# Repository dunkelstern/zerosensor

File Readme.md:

# Raspberry Pi Zero Sensor breakout board

<br />This work is licensed under a <a rel="license" href="http://creativecommons.org/licenses/by-sa/4.0/">Creative Commons Attribution-ShareAlike 4.0 International License</a>.

- 2 Level-Shifted SPI Ports
- 1 Level-Shifted I2C Port (Stemma/Grove/Quiic compatible)
- 1 Level-Shifted UART Port
- 4 Analog Inputs with onboard I2C ADC (MAX116xx-Series)
- 1 I2S Port (3.3V only)
- 2 Buttons on GPIO Pins
- 1 LED on GPIO Pin
- Power MOSFET on PWM Pin (Max 20V 8.5A)
- (optional) External Power In via Power MOSFET Screw-Terminal with 5V Regulator
- (optional) Extra 3.3V LDO to avoid introducing fault current into Raspi 3.3V rail
- (optional) Hat EEPROM for auto-configuration

## Before use

**Please read this document before use, you have to set some solder jumpers to use the board!**

- [BOM](bom.html)
- Gerbers are in `gerber` sub-directory
- SVG renders for manual UV exposing copper plated boards for etching yourself are in `svg` (be aware: this PCB has 86 vias and all through holes are supposed to be plated through!)
- Assembly files with values of resistors, etc are in `assembly`
- You can find a STEP file in `assembly` too

## SPI

There are 2 SPI ports broken out, they share MISO, MOSI and SCK lines and the chip enable
pins of the Raspberry PI (CE0 and CE1) are split between the ports. I used bigger connectors
here to differenciate the Ports from the smaller I2C and UART ports.

You have to select the voltage level on these ports by bridging the "SPI" solder jumper to
the desired voltage.

## I2C

The I2C port is Stemma/Grove/Quiic compatible. All lines are level-translated to the voltage
selected with the "I2C/UART" solder jumper.

## UART

The UART is connected to the first UART of the Raspberry Pi, usually you get a debug console
on that port, but you can use it for other things too, you just have to disable the `Getty`
process on the UART. The UART shares the voltage selection with the I2C port, so if you need
power from the UART socket you'll have to bridge that solder jumper to the correct voltage.

## Analog Inputs

The PCB footprint has been modified to accept any chips from the MAX116xx-Series.
You can use any SOIC8 or SOT23-8 chip from the series, both will fit the board.
The power supply for the chip is configurable via solder jumper "ADC Voltage" (3.3V or 5V) on
the back side of the PCB.

The analog inputs are clamped to 3.6V with Zener diodes to avoid bricking the ADC when
connecting something wrong or using long cables and getting voltage spikes.

**Attention**: Modify values of the voltage dividers accordingly!

### Voltage dividers for Analog Inputs

R22/23 (1k and 1.8k) are calculated for 5V, leave R23 open and replace R22 with zero Ohm link
for 3.3V supply.

Select the voltage divider for the inputs based on the reference voltage of the used ADC chip:

- 2.048 V: a = 24k, b = 15k
- 4.096 V: a = 47k, b = 150k

Group A is R11, R12, R17, R18, group B is R9, R10, R15, R16.

## I2S

I2S is a digital audio bus, it can support two channels and up to 48kHz samplerate. This
port has been broken out for use with an I2S MEMS microphone. It supports only 3.3V.

## Buttons

Two buttons on GPIO ports 22 and 23 are supplied. They have pull-up resistors on board, so the
read level is inverse: GPIO high = button not pressed!

## LED

The LED is on GPIO port 4, use a low power LED here, the resistor is calculated for 15 mA.

## Power MOSFET

The Power MOSFET is a P-Channel mosfet with a NPN transistor for voltage amplification. The PCB
traces are laid out for 8.5A (thermal limit! traces will heat up to 60 degrees Celsius with that
amount of power) but the MOSFET may switch 35A maximum (add cooling!). Be aware the Terminal block
might be the limiting factor as it is only specified for 5A continous load.

The NPN transistor as well as the optional LDO (see below) can only handle 20V so be aware to not
connect anything above that.

There is a small reverse clamping diode (max. 4A) if you want to switch a small inductive load like
a relay.

The Power MOSFET Terminal block may be used to power the Raspberry Pi, for more information see below.

## External Power

If you can not power the Raspberry Pi from an USB power supply you can install the 5V LDO
(U4, C6, C7) and bridge the "Ext Power" solder jumper to "reverse"-power the PI from the
Power MOSFET terminal block.

**Attention**: The LDO can only handle up to 1A of current (it will get hot in that case!) and a maximum of 20V. The minimum voltage to supply to run stable is about 6.5V.

The Raspberry Pi will use 250mA of the 1A power budget, so you have approximately 700mA to power
your sensors and actuators.

## 3.3V LDO

If you want to isolate your sensors/actuators from the Raspberry Pi 3.3V power rail to avoid
putting garbage on those voltage rails (probably crashing the Pi) or if you need a clean supply
that is not influenced by the Pi that much you can add the 3.3V LDO (Parts U5, C8, C9) and bridge
the "3.3V Select" solder jumber to "Reg" to use that regulator instead of the one on the Raspberry
Pi board.

If you want to use the internal regulator of the Pi, bridge this jumper to "Pi", else you will not
have any 3.3V supply on the board and no port will be functioning as the Level-shifters and the
ADC will use the 3.3V supply.

The LDO has a capacity of 1A, but you will not be able to use that much power neither from the Pi (250mA will be used by the Pi itself, ca 700mA are available) nor from the external LDO (this
depends on the 5V supply, if you're using External Power the 3.3V LDO is behind the 5V LDO, so both
share the 700mA that are available from that, if you're using USB power it depends on what that
power source is capable of).

## Hat EEPROM

There is an optional Hat EEPROM for autoconfiguration on the I2C0 bus of the Raspberry Pi, on boot
the Pi reads the contents of that EEPROM chip to pre-configure the GPIO header and load drivers.

If you want to use this you'll have to program the EEPROM using the Raspberry Pi itself. On top of
the PCB you can see two test-points with the letters "WR" beside them. If you bridge those the EEPROM
will get writeable. You'll just have to activate the I2C0 bus and use the
[Raspberry Pi Hat utilities](https://github.com/raspberrypi/hats/tree/master/eepromutils) to create
a ROM image for the chip.

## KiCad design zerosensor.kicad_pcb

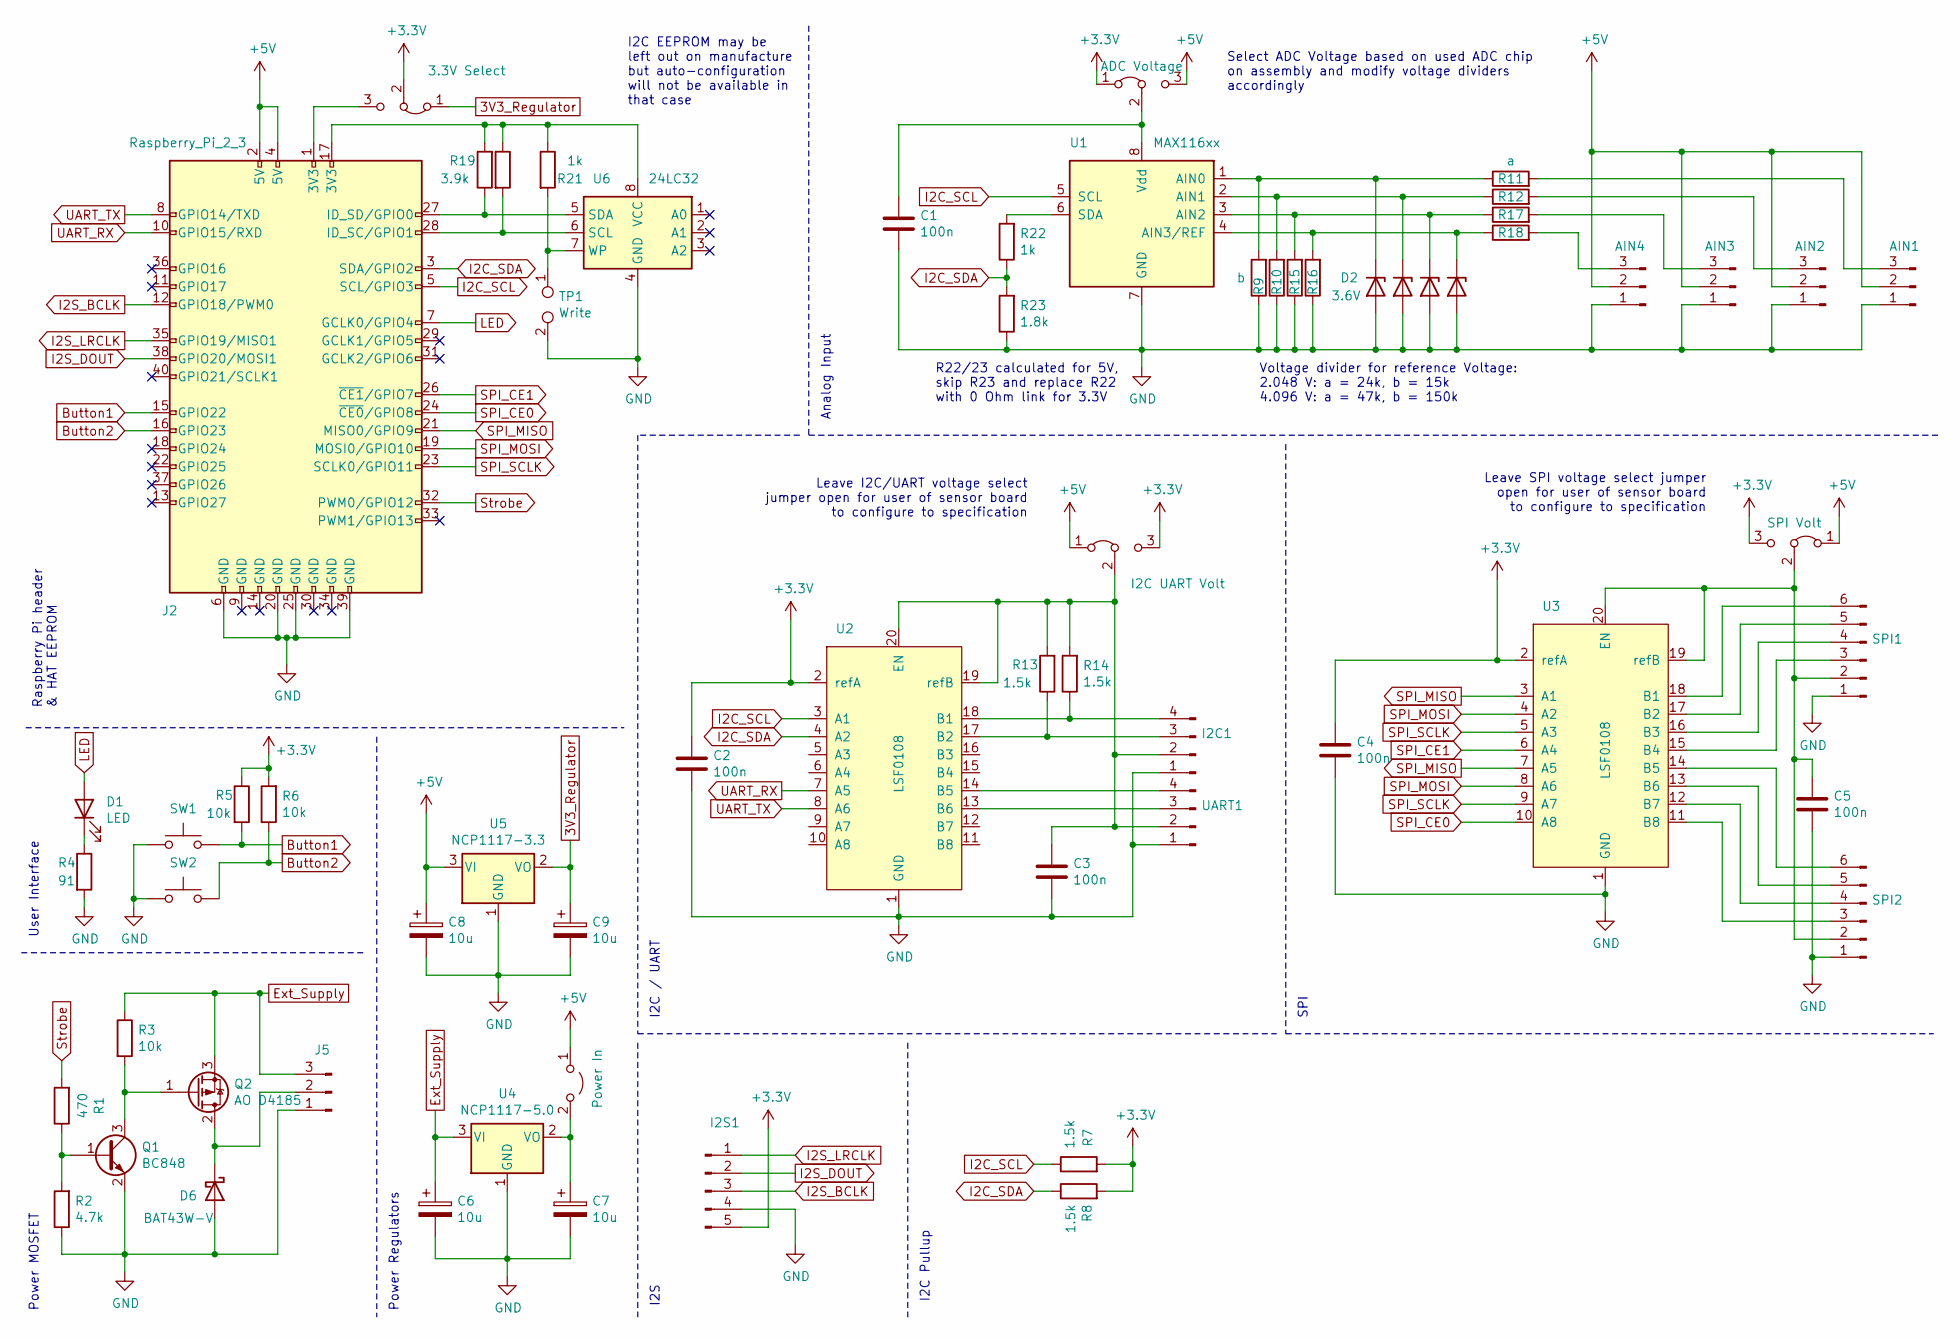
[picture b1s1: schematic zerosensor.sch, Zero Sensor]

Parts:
AIN1: AIN1; JST_PH_B3B-PH-K_1x03_P2.00mm_Vertical
AIN2: AIN2; JST_PH_B3B-PH-K_1x03_P2.00mm_Vertical
AIN3: AIN3; JST_PH_B3B-PH-K_1x03_P2.00mm_Vertical
AIN4: AIN4; JST_PH_B3B-PH-K_1x03_P2.00mm_Vertical
C1, C2, C3, C4, C5: 100n; C_0805_2012Metric_Pad1.18x1.45mm_HandSolder
C6, C7, C8, C9: 10u; C_1206_3216Metric_Pad1.33x1.80mm_HandSolder
D1: LED; LED_D3.0mm
D2, D3, D4, D5: 3.6V; D_MiniMELF
D6: BAT43W-V; D_SOD-123
I2C1: I2C; JST_PH_B4B-PH-K_1x04_P2.00mm_Vertical
I2S1: I2S; PinHeader_1x05_P2.54mm_Vertical
J2: Raspberry_Pi_2_3; PinHeader_2x20_P2.54mm_Horizontal
J5: Strobe; PhoenixContact_MCV_1,5_3-G-3.5_1x03_P3.50mm_Vertical
JP1: I2C UART Volt; PinHeader_1x03_P2.54mm_Vertical
JP2: Power In; SolderJumper-2_P1.3mm_Open_TrianglePad1.0x1.5mm
JP3: SPI Volt; PinHeader_1x03_P2.54mm_Vertical
JP4: 3.3V Select; PinHeader_1x03_P2.54mm_Vertical
JP5: ADC Voltage; SolderJumper-3_P1.3mm_Open_RoundedPad1.0x1.5mm_NumberLabels
Q1: BC848; SOT-23
Q2: AO D4185; TO-252-2
R1: 470; R_1206_3216Metric_Pad1.30x1.75mm_HandSolder
R2: 4.7k; R_1206_3216Metric_Pad1.30x1.75mm_HandSolder
R3, R5, R6: 10k; R_1206_3216Metric_Pad1.30x1.75mm_HandSolder
R4: 91; R_1206_3216Metric_Pad1.30x1.75mm_HandSolder
R7, R8, R13, R14: 1.5k; R_1206_3216Metric_Pad1.30x1.75mm_HandSolder
R9, R10, R15, R16: b; R_1206_3216Metric_Pad1.30x1.75mm_HandSolder
R11, R12, R17, R18: a; R_1206_3216Metric_Pad1.30x1.75mm_HandSolder
R19, R20: 3.9k; R_1206_3216Metric_Pad1.30x1.75mm_HandSolder
R21, R22: 1k; R_1206_3216Metric_Pad1.30x1.75mm_HandSolder
R23: 1.8k; R_1206_3216Metric_Pad1.30x1.75mm_HandSolder
SPI1: SPI1; JST_XH_B6B-XH-A_1x06_P2.50mm_Vertical
SPI2: SPI2; JST_XH_B6B-XH-A_1x06_P2.50mm_Vertical
SW1, SW2: SW_Push; SW_PUSH_6mm_H8mm
TP1: Write; TestPoint_2Pads_Pitch2.54mm_Drill0.8mm
U1: MAX116xx; MSOP-8_3x3mm_P0.65mm
U2, U3: LSF0108; TSSOP-20_4.4x6.5mm_P0.65mm
U4: NCP1117-5.0; SOT-223-3_TabPin2
U5: NCP1117-3.3; SOT-223-3_TabPin2
U6: 24LC32; SOIC-8_3.9x4.9mm_P1.27mm
UART1: UART; JST_PH_B4B-PH-K_1x04_P2.00mm_Vertical

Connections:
3V3_Regulator: C9.1, JP4.1 (A), U5.2 (VO)
+3V3: C2.1, C4.1, I2S1.5, JP1.3 (B), JP3.3 (B), JP4.2 (C), JP5.1 (A), R5.1, R6.2, R7.2, R8.2, U2.2 (refA), U3.2 (refA)
+5V: AIN1.2, AIN2.2, AIN3.2, AIN4.2, C8.1, J2.2 (5V), J2.4 (5V), JP1.1 (A), JP2.1 (A), JP3.1 (A), JP5.3 (B), U5.3 (VI)
Button1: J2.15 (GPIO22), R5.2, SW1.2
Button2: J2.16 (GPIO23), R6.1, SW2.2
Ext_Supply: C6.1, J5.3, Q2.3 (S), R3.1, U4.3 (VI)
GND: AIN1.1, AIN2.1, AIN3.1, AIN4.1, C1.2, C2.2, C3.2, C4.2, C5.2, C6.2, C7.2, C8.2, C9.2, D2.2 (A), D3.2 (A), D4.2 (A), D5.2 (A), D6.2 (A), I2C1.1, I2S1.4, J2.6 (GND), J2.20 (GND), J2.25 (GND), J2.39 (GND), J5.1, Q1.2 (E), R2.1, R4.2, R9.1, R10.1, R15.1, R16.1, R23.1, SPI1.1, SPI2.1, SW1.1, SW2.1, TP1.2, U1.7 (GND), U2.1 (GND), U3.1 (GND), U4.1 (GND), U5.1 (GND), U6.4 (GND), UART1.1
I2C_SCL: J2.5 (SCL/GPIO3), R7.1, U1.5 (SCL), U2.3 (A1)
I2C_SDA: J2.3 (SDA/GPIO2), R8.1, R22.1, R23.2, U2.4 (A2)
I2S_BCLK: I2S1.3, J2.12 (GPIO18/PWM0)
I2S_DOUT: I2S1.2, J2.38 (GPIO20/MOSI1)
I2S_LRCLK: I2S1.1, J2.35 (GPIO19/MISO1)
LED: D1.2 (A), J2.7 (GCLK0/GPIO4)
unnamed: AIN1.3, R11.2
unnamed: AIN2.3, R12.2
unnamed: AIN3.3, R17.2
unnamed: AIN4.3, R18.2
unnamed: C1.1, JP5.2 (C), U1.8 (Vdd)
unnamed: C3.1, I2C1.2, JP1.2 (C), R13.2, R14.2, U2.19 (refB), U2.20 (EN), UART1.2
unnamed: C5.1, JP3.2 (C), SPI1.2, SPI2.2, U3.19 (refB), U3.20 (EN)
unnamed: C7.1, JP2.2 (B), U4.2 (VO)
unnamed: D1.1 (K), R4.1
unnamed: D2.1 (K), R9.2, R11.1, U1.1 (AIN0)
unnamed: D3.1 (K), R10.2, R12.1, U1.2 (AIN1)
unnamed: D4.1 (K), R15.2, R17.1, U1.3 (AIN2)
unnamed: D5.1 (K), R16.2, R18.1, U1.4 (AIN3/REF)
unnamed: D6.1 (K), J5.2, Q2.2 (D)
unnamed: I2C1.3, R13.1, U2.17 (B2)
unnamed: I2C1.4, R14.1, U2.18 (B1)
unnamed: J2.1 (3V3), JP4.3 (B)
unnamed: J2.17 (3V3), R19.2, R20.1, R21.1, U6.8 (VCC)
unnamed: J2.27 (ID_SD/GPIO0), R19.1, U6.5 (SDA)
unnamed: J2.28 (ID_SC/GPIO1), R20.2, U6.6 (SCL)
unnamed: Q1.1 (B), R1.1, R2.2
unnamed: Q1.3 (C), Q2.1 (G), R3.2
unnamed: R21.2, TP1.1, U6.7 (WP)
unnamed: R22.2, U1.6 (SDA)
unnamed: SPI1.3, U3.15 (B4)
unnamed: SPI1.4, U3.16 (B3)
unnamed: SPI1.5, U3.17 (B2)
unnamed: SPI1.6, U3.18 (B1)
unnamed: SPI2.3, U3.11 (B8)
unnamed: SPI2.4, U3.12 (B7)
unnamed: SPI2.5, U3.13 (B6)
unnamed: SPI2.6, U3.14 (B5)
unnamed: U2.13 (B6), UART1.3
unnamed: U2.14 (B5), UART1.4
SPI_CE0: J2.24 (~CE0~/GPIO8), U3.10 (A8)
SPI_CE1: J2.26 (~CE1~/GPIO7), U3.6 (A4)
SPI_MISO: J2.21 (MISO0/GPIO9), U3.3 (A1), U3.7 (A5)
SPI_MOSI: J2.19 (MOSI0/GPIO10), U3.4 (A2), U3.8 (A6)
SPI_SCLK: J2.23 (SCLK0/GPIO11), U3.5 (A3), U3.9 (A7)
Strobe: J2.32 (PWM0/GPIO12), R1.2
UART_RX: J2.10 (GPIO15/RXD), U2.7 (A5)
UART_TX: J2.8 (GPIO14/TXD), U2.8 (A6)

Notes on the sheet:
R22/23 calculated for 5V, skip R23 and replace R22 with 0 Ohm link for 3.3V
Voltage divider for reference Voltage: 2.048 V: a = 24k, b = 15k 4.096 V: a = 47k, b = 150k
Analog Input
SPI
I2C / UART
Raspberry Pi header & HAT EEPROM
Power Regulators
Power MOSFET
User Interface
I2S
I2C Pullup
Select ADC Voltage based on used ADC chip on assembly and modify voltage dividers accordingly
Leave I2C/UART voltage select jumper open for user of sensor board to configure to specification
Leave SPI voltage select jumper open for user of sensor board to configure to specification
I2C EEPROM may be left out on manufacture but auto-configuration will not be available in that case

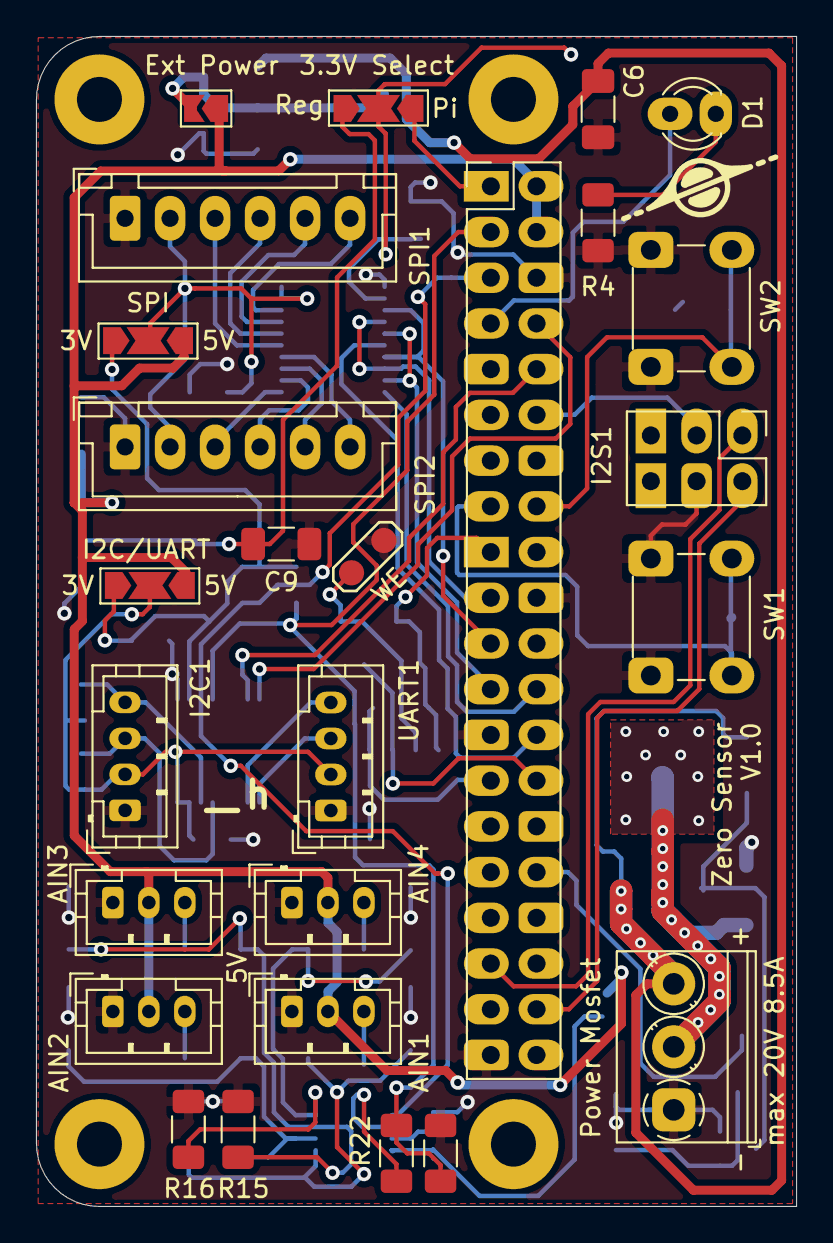
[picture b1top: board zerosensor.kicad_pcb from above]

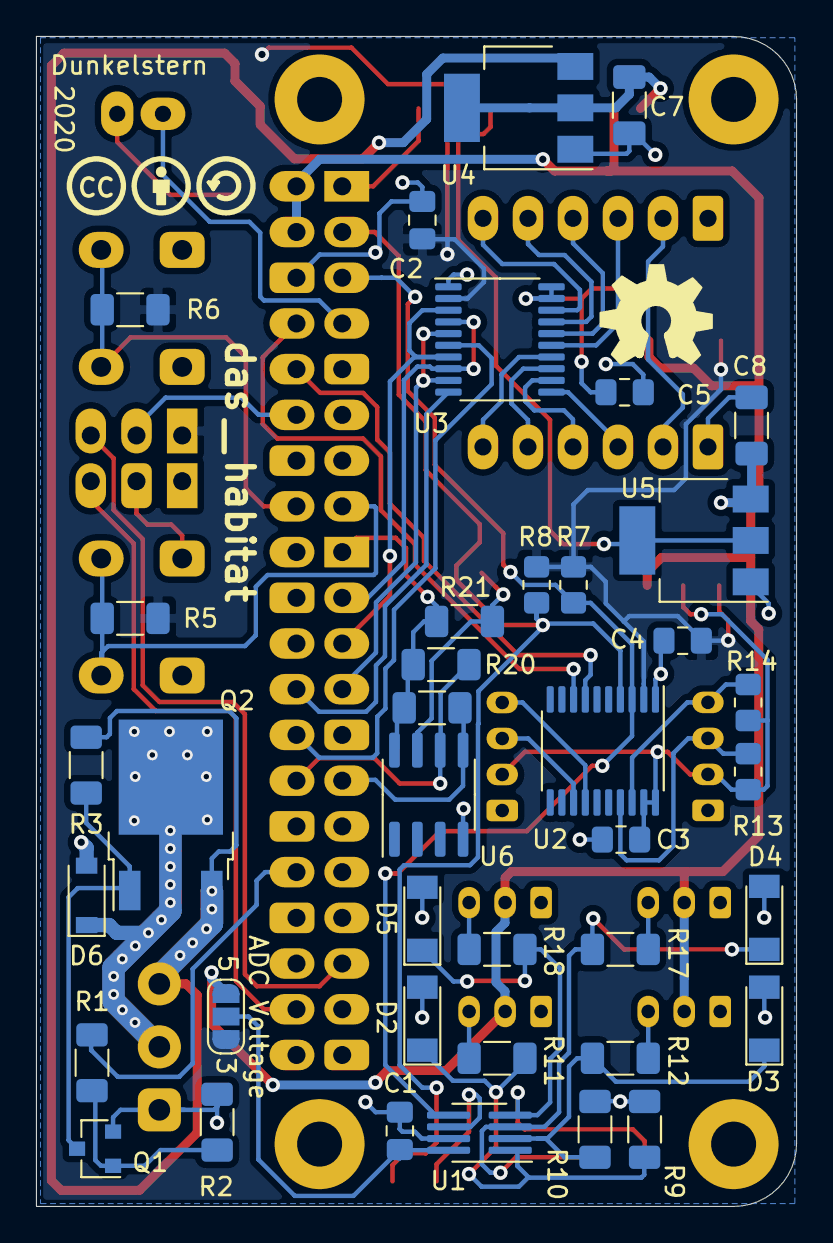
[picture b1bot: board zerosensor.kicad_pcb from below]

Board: 2 copper layers, 42.2 x 65.0 mm, 65 parts (39 on the bottom side), 55 nets.

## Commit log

2020-11-30 Add level shifter symbol
2020-11-30 Add logo footprint lib
2020-11-30 Add schematics and PCB layout
2020-11-30 Add BOM
2020-11-30 Add readme
2020-11-30 Add Gerbers
2020-11-30 Add UV masks
2020-11-30 Add assembly drawings and 3D model
2020-11-30 Add license
2020-11-30 Add board render

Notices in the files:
parts and their libraries:
Creative Commons Sharealike
CreativeCommons Attribution (Smaller Version)
